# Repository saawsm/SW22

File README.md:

# SW22 - A modular E-Stim

---
**The SW22 is deprecated. See the [SW32 E-Stim](https://github.com/saawsm/SW32) for a better alternative.**

*This project is a work in-progress. Changes to the design might occur. Order PCBs at your own risk..*

---

## About
The SW22 is a modular E-Stim box based on the [ZC95](https://github.com/CrashOverride85/zc95) and the [WT-312](https://github.com/WendyTeslaburger/WT-312). 
It has a similar form factor and output design to the MK312-BT (which in turn is a clone of the ET-312B).

An <abbr title="ESP32-WROOM-32">ESP32</abbr> module is used for high level control (front panel controls, display, Bluetooth audio, etc) of the device, while an RP2040 microcontroller (RPi Pico) is used as a co-processor for pulse/routine generation (taking advantage of [PIO](https://raspberrypi.github.io/pico-sdk-doxygen/group__hardware__pio.html#details)). The firmware is open source and written in C.

Compared to the MK312-BT, it has two extra output channels, four auxiliary inputs, and four triggers. 

## Features
* Bluetooth A2DP*
* RS232 front panel serial
* 2x TRS 3.5mm Aux channels with expansion board support (e.g. Stereo Audio + Mono Microphone, RS232 Remote)
* 2x TRS 3.5mm Trigger channels
* Tri polar (+, GND, -) output channel support
* Modular output drivers per channel (Think: Sparkfun, Adafruit, etc.) incl. modular driver board.
* Individual channel sensing via quad 12-bit ADC
* 1.8" Color TFT display
* Support for an internal 0.96" I2C OLED display (e.g. debugging/testing)
* 256kb EEPROM for configuration
* Battery voltage monitoring
* Charge sense (Barrel jack voltage monitoring)

## Overview
The SW22 consists of following PCBs:
* Front Panel Cover - No traces, just the cosmetic front panel with text. Could be 3D printed or laser cut.
* Front Panel - I2C based expansion board with 4x POTs with associated ADC, 1x rotary encoder, 4x tactile buttons, 1x buzzer, and 8x addressable RGB LEDs.
* Base Board - Provides system power, battery charging, expansion, Bluetooth, front panel interface, and general control.
* Driver Board - Provides low-level control over channel output modules.
* Output Modules - Generates the E-Stim for each channel. A module per channel, controlled by the driver board. 
* Expansion Module (Optional) - Allows advanced configuration of Aux channels (e.g. Audio+Microphone)

The main reason for having modular PCBs is for flexibility and long term cost saving. Most of the cost and time that is involved in the project is the firmware, case, display, controls, etc. So being able to reuse parts when changing the design (e.g. new output modules, driver board, etc) should help keep time and cost down.

Additionally, the SW22 was designed with the front panel and display being optional accessories. Anything that can be achieved on the front panel, can be done via Bluetooth/WiFi. The driver board can be used as a standalone module (Think: Sparkfun, Adafruit, etc.).

## Build Notes
The majority of this build is SMT. I have tried to keep parts large enough (0603 and above) for manual pick and place. However, for a few components, no alternative was available (e.g. Driver board uses MSOP/VSSOP packages).

Most SMD components used are available from Mouser and LCSC. Front panel components being mostly available at places that aren't LCSC (pots, encoders, audio jacks, etc).

Some components have a thermal pad that will require a reflow oven or using hot air reflow soldering.

## [Schematics](schematics/)

## [Gerbers](gerbers/)
Gerbers are created for use with JLCPCB. P&P POS files untested/missing (since I assemble the PCBs myself).

## Firmware
The firmware is open source and written in C. You can find the source code in the [swef](https://github.com/saawsm/swef) and [swx](https://github.com/saawsm/swx) repositories.

`swef` and `swx` don't support SPI used by the SW22 for connection between the base and driver boards. Basic functionality requires adding additional bodge wires (SDA and SCL) between the base and driver boards.

This change was done to simplify communications and to prepare for the successor [SW32](https://github.com/saawsm/SW32) box.

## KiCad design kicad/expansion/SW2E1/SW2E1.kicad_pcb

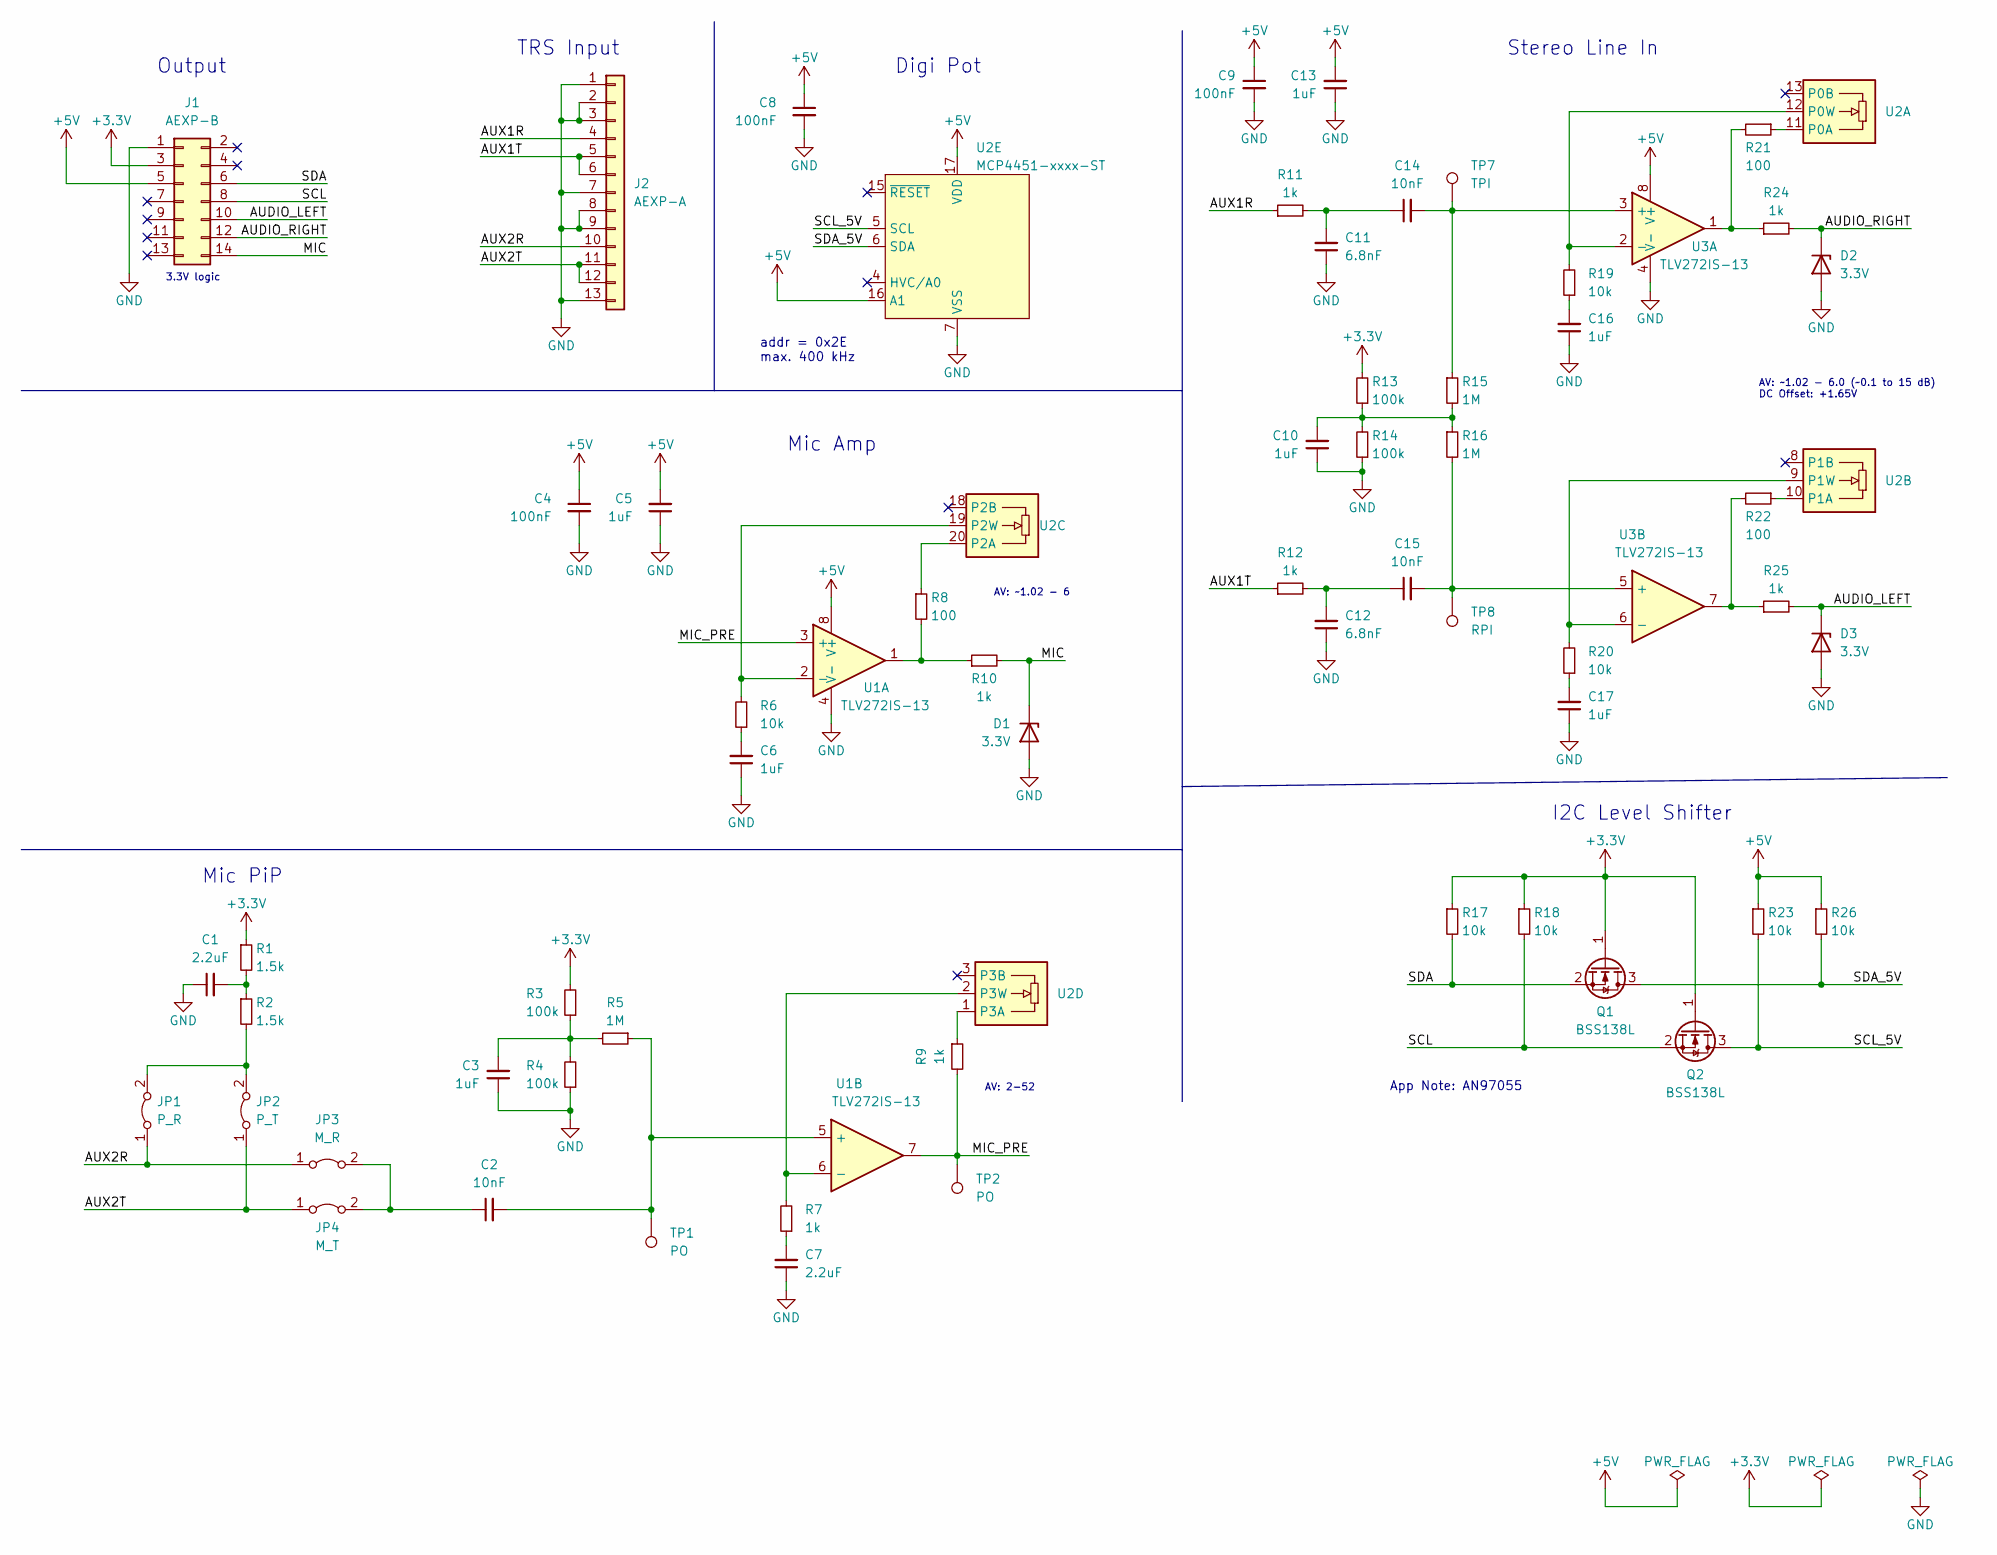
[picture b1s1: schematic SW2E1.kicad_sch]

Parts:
C1, C7: 2.2uF; C_0603_1608Metric
C2, C14, C15: 10nF; C_0603_1608Metric
C3, C5, C6, C10, C13, C16, C17: 1uF; C_0603_1608Metric
C4, C8, C9: 100nF; C_0603_1608Metric
C11, C12: 6.8nF; C_0603_1608Metric
D1, D2, D3: 3.3V; D_SOD-123F
J1: AEXP-B; PinHeader_2x07_P2.54mm_Vertical
J2: AEXP-A; PinHeader_1x13_P2.54mm_Vertical
JP1: P_R; PinHeader_1x02_P2.54mm_Vertical
JP2: P_T; PinHeader_1x02_P2.54mm_Vertical
JP3: M_R; PinHeader_1x02_P2.54mm_Vertical
JP4: M_T; PinHeader_1x02_P2.54mm_Vertical
Q1, Q2: BSS138L; SOT-23
R1, R2: 1.5k; R_0603_1608Metric
R3, R4, R13, R14: 100k; R_0603_1608Metric
R5, R15, R16: 1M; R_0603_1608Metric
R6, R17, R18, R19, R20, R23, R26: 10k; R_0603_1608Metric
R7, R9, R10, R11, R12, R24, R25: 1k; R_0603_1608Metric
R8, R21, R22: 100; R_0603_1608Metric
TP1, TP2: PO; TestPoint_Pad_D1.5mm
TP7: TPI; TestPoint_Pad_D1.5mm
TP8: RPI; TestPoint_Pad_D1.5mm
U1, U3: TLV272IS-13; SOIC-8_3.9x4.9mm_P1.27mm
U2: MCP4451-xxxx-ST; TSSOP-20_4.4x6.5mm_P0.65mm

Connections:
+3.3V: J1.3, Q1.1 (G), Q2.1 (G), R1.1, R3.2, R13.2, R17.1, R18.1
+5V: C4.1, C5.2, C8.1, C9.1, C13.2, J1.5, R23.1, R26.1, U1.8 (V+), U2.16 (A1), U2.17 (VDD), U3.8 (V+)
/AUDIO_LEFT: D3.1 (K), J1.10, R25.2
/AUDIO_RIGHT: D2.1 (K), J1.12, R24.2
/AUX1R: J2.4, R11.1
/AUX1T: J2.5, J2.6, R12.1
/AUX2R: J2.10, JP1.1 (A), JP3.1 (A)
/AUX2T: J2.11, J2.12, JP2.1 (A), JP4.1 (A)
/MIC: D1.1 (K), J1.14, R10.2
/MIC_PRE: R9.2, TP2.1, U1.3 (+), U1.7
/SCL: J1.8, Q2.2 (S), R18.2
/SCL_5V: Q2.3 (D), R23.2, U2.5 (SCL)
/SDA: J1.6, Q1.2 (S), R17.2
/SDA_5V: Q1.3 (D), R26.2, U2.6 (SDA)
GND: C1.1, C3.1, C4.2, C5.1, C6.1, C7.1, C8.2, C9.2, C10.1, C11.1, C12.1, C13.1, C16.1, C17.1, D1.2 (A), D2.2 (A), D3.2 (A), J1.1, J2.1, J2.2, J2.3, J2.7, J2.8, J2.9, J2.13, R4.1, R14.1, U1.4 (V-), U2.7 (VSS), U3.4 (V-)
unnamed: C1.2, R1.2, R2.1
unnamed: C2.1, JP3.2 (B), JP4.2 (B)
unnamed: C2.2, R5.1, TP1.1, U1.5 (+)
unnamed: C3.2, R3.1, R4.2, R5.2
unnamed: C6.2, R6.1
unnamed: C7.2, R7.1
unnamed: C10.2, R13.1, R14.2, R15.2, R16.1
unnamed: C11.2, C14.1, R11.2
unnamed: C12.2, C15.1, R12.2
unnamed: C14.2, R15.1, TP7.1, U3.3 (+)
unnamed: C15.2, R16.2, TP8.1, U3.5 (+)
unnamed: C16.2, R19.1
unnamed: C17.2, R20.1
unnamed: JP1.2 (B), JP2.2 (B), R2.2
unnamed: R6.2, U1.2 (-), U2.19 (P2W)
unnamed: R7.2, U1.6 (-), U2.2 (P3W)
unnamed: R8.1, U2.20 (P2A)
unnamed: R9.1, U2.1 (P3A)
unnamed: R8.2, R10.1, U1.1
unnamed: R19.2, U2.12 (P0W), U3.2 (-)
unnamed: R20.2, U2.9 (P1W), U3.6 (-)
unnamed: R21.1, U2.11 (P0A)
unnamed: R21.2, R24.1, U3.1
unnamed: R22.1, U2.10 (P1A)
unnamed: R22.2, R25.1, U3.7

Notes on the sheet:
I2C Level Shifter
App Note: AN97055
addr = 0x2E max. 400 kHz
TRS Input
Digi Pot
Mic PiP
Stereo Line In
Mic Amp
AV: ~1.02 - 6.0 (~0.1 to 15 dB) DC Offset: +1.65V
Output
AV: ~1.02 - 6
3.3V logic
AV: 2-52

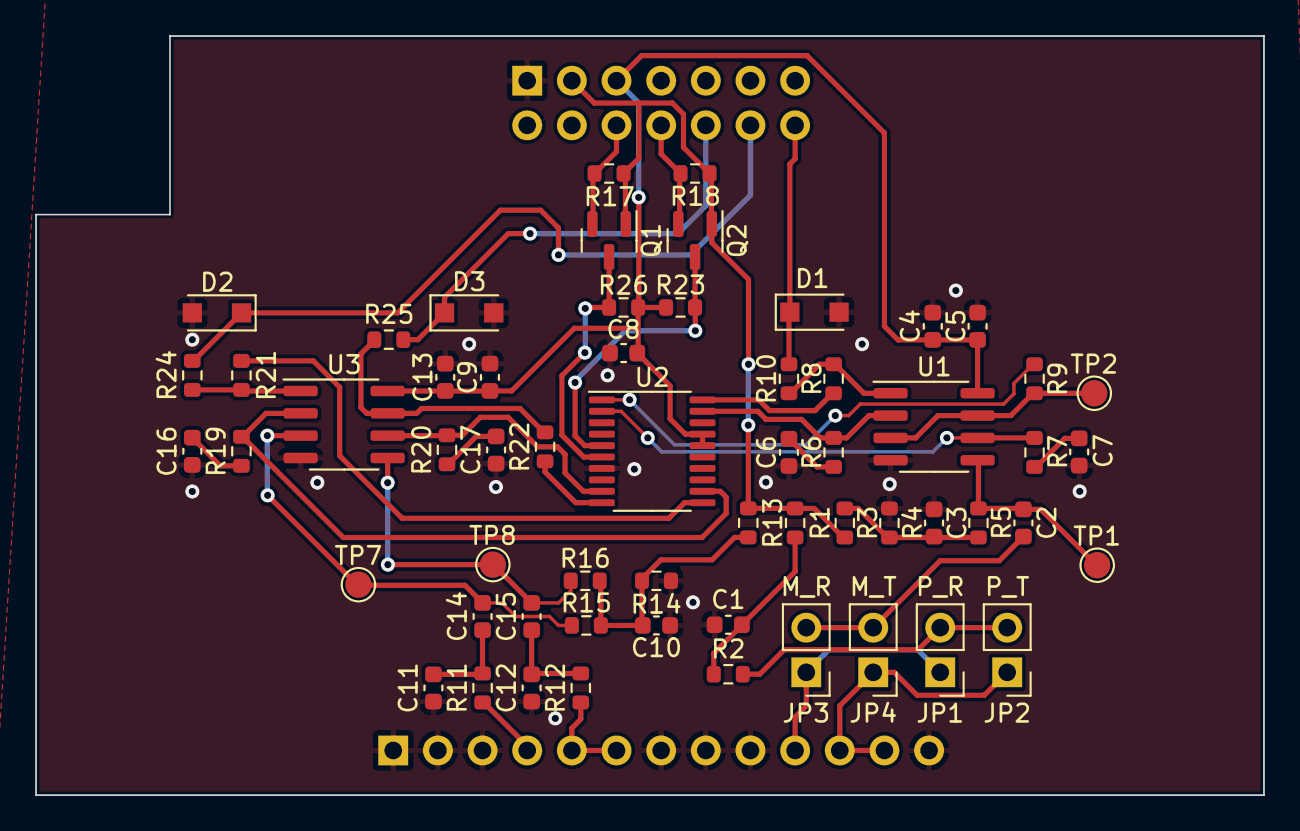
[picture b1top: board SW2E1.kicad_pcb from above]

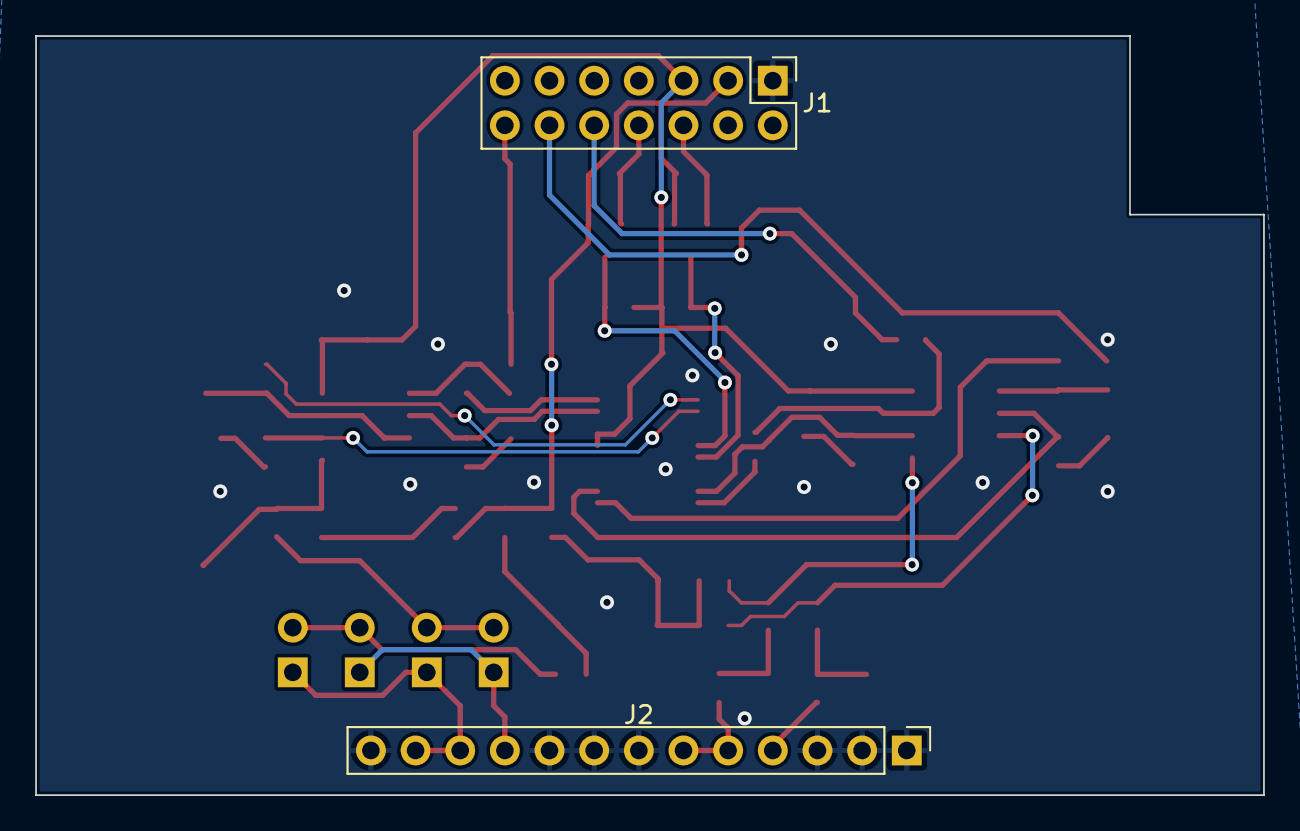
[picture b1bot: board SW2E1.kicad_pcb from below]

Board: 2 copper layers, 69.9 x 43.2 mm, 61 parts (2 on the bottom side), 40 nets.

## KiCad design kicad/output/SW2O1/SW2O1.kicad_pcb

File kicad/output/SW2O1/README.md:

## SW2O1 - Single Channel Output Module

This is a single channel E-Stim output module. It tries to mimic the output stage of the well-known Erostec ET312, or better, the MK-312.

The design of this module was based on the [WT-312](https://github.com/WendyTeslaburger/WT-312).

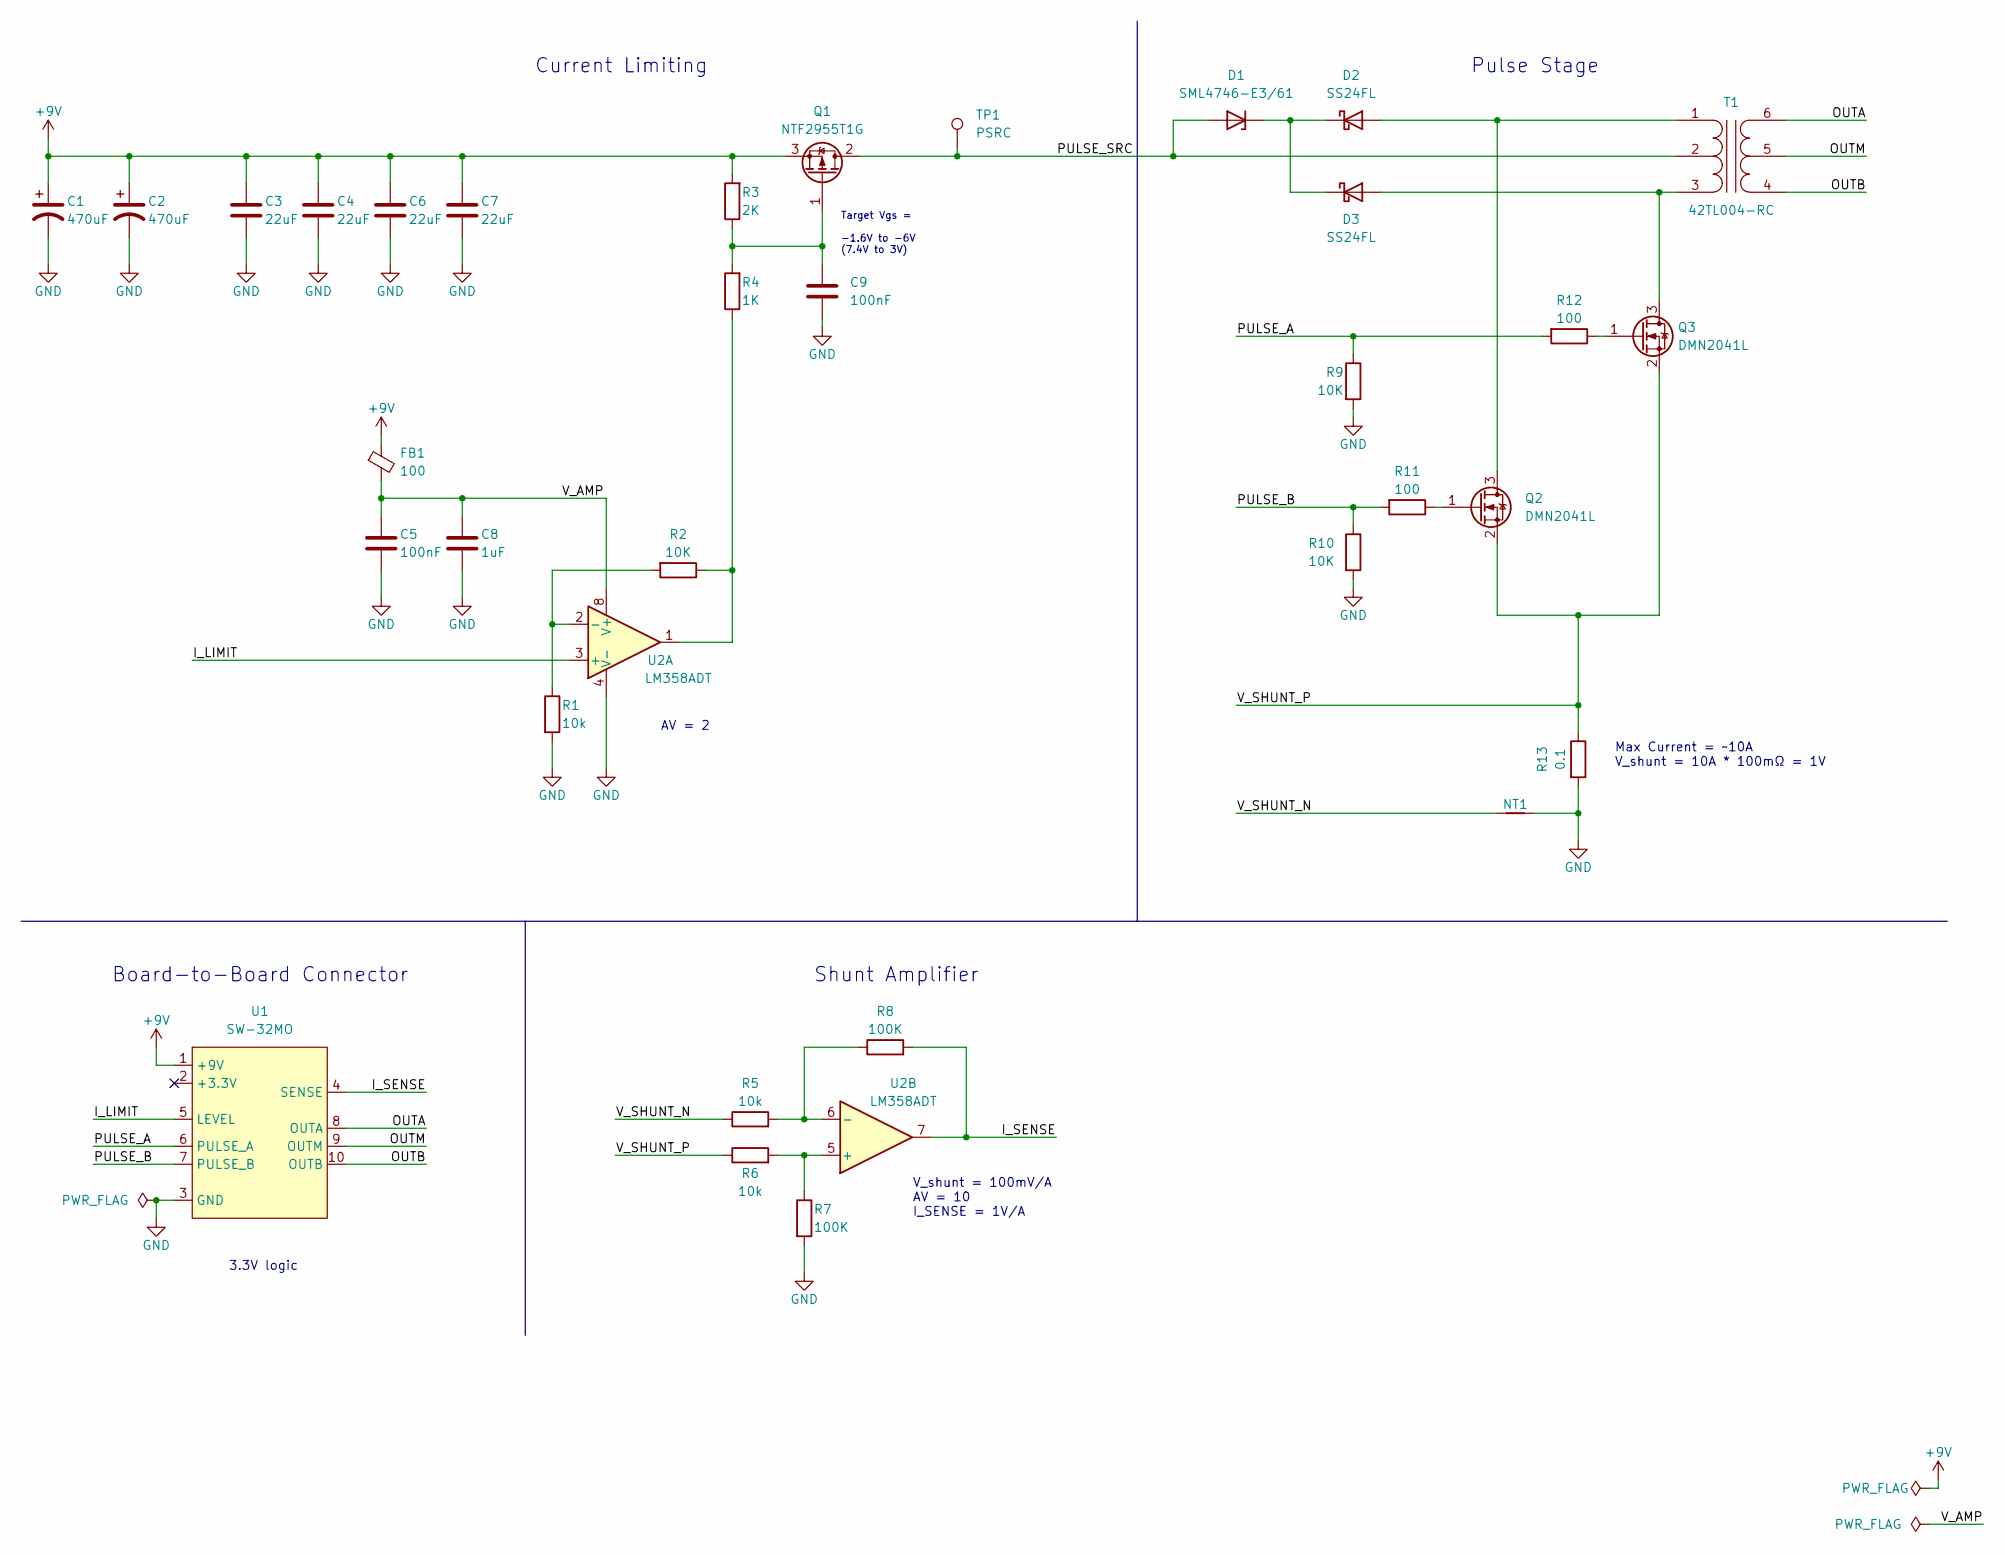
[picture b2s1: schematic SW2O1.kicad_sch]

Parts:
C1, C2: 470uF; CP_Radial_D8.0mm_P3.50mm; MPN 477CKE016M
C3, C4, C6, C7: 22uF; C_1210_3225Metric; MPN CL32A226KAJNNNE
C5, C9: 100nF; C_0603_1608Metric; MPN CL10B104KB8NNWC
C8: 1uF; C_0603_1608Metric; MPN CL10B105KA8NFNC
D1: SML4746-E3/61; D_SMA; MPN SML4746-E3/61
D2: SS24FL; D_SOD-123F; MPN SS24FL; LCSC C894433
D3: SS24FL; D_SOD-123F; MPN SS24FL; MOUSER 512-SS24FL
FB1: 100; R_0603_1608Metric; MPN BLM18KG101TN1D
NT1: 0.5 mm; NetTie-2_SMD_Pad0.5mm
Q1: NTF2955T1G; SOT-223-3_TabPin2; MPN NTF2955T1G
Q2, Q3: DMN2041L; SOT-23; MPN DMN2041L
R1, R5, R6: 10k; R_0603_1608Metric; MPN RC0603FR-0710KL
R2, R9, R10: 10K; R_0603_1608Metric; MPN RC0603FR-0710KL
R3: 2K; R_0603_1608Metric; MPN RC0603FR-072KL
R4: 1K; R_0603_1608Metric; MPN RC0603FR-071KL
R7, R8: 100K; R_0603_1608Metric; MPN RC0603FR-07100KL
R11, R12: 100; R_0603_1608Metric; MPN RC0603FR-07100RL
R13: 0.1; R_1206_3216Metric; MPN ERJ-8BWFR100V
T1: 42TL004-RC; 42TL; MPN 42TL004-RC
TP1: PSRC; TestPoint_Pad_D1.5mm
U1: SW-32MO; SW32-MO_Header
U2: LM358ADT; SOIC-8_3.9x4.9mm_P1.27mm; MPN LM358ADT

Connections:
+9V: C1.1, C2.1, C3.1, C4.1, C6.1, C7.1, FB1.1, Q1.3 (S), R3.2, U1.1 (+9V)
/I_LIMIT: U1.5 (LEVEL), U2.3 (+)
/I_SENSE: R8.2, U1.4 (SENSE), U2.7
/OUTA: T1.6 (S2), U1.8 (OUTA)
/OUTB: T1.4 (S1), U1.10 (OUTB)
/OUTM: T1.5 (SM), U1.9 (OUTM)
/PULSE_A: R9.1, R12.2, U1.6 (PULSE_A)
/PULSE_B: R10.1, R11.2, U1.7 (PULSE_B)
/PULSE_SRC: D1.2 (A), Q1.2 (D), T1.2 (PM), TP1.1
/V_AMP: C5.1, C8.1, FB1.2, U2.8 (V+)
/V_SHUNT_N: NT1.1, R5.1
/V_SHUNT_P: Q2.2 (S), Q3.2 (S), R6.1, R13.1
GND: C1.2, C2.2, C3.2, C4.2, C5.2, C6.2, C7.2, C8.2, C9.1, NT1.2, R1.2, R7.2, R9.2, R10.2, R13.2, U1.3 (GND), U2.4 (V-)
unnamed: C9.2, Q1.1 (G), R3.1, R4.2
unnamed: D1.1 (K), D2.1 (K), D3.1 (K)
unnamed: D2.2 (A), Q2.3 (D), T1.1 (PR1)
unnamed: D3.2 (A), Q3.3 (D), T1.3 (PR2)
unnamed: Q2.1 (G), R11.1
unnamed: Q3.1 (G), R12.1
unnamed: R1.1, R2.2, U2.2 (-)
unnamed: R2.1, R4.1, U2.1
unnamed: R5.2, R8.1, U2.6 (-)
unnamed: R6.2, R7.1, U2.5 (+)

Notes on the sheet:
Max Current = ~10A V_shunt = 10A * 100mΩ = 1V
Board-to-Board Connector
V_shunt = 100mV/A AV = 10 I_SENSE = 1V/A
AV = 2
Shunt Amplifier
Pulse Stage
Target Vgs = -1.6V to -6V (7.4V to 3V)
Current Limiting
3.3V logic

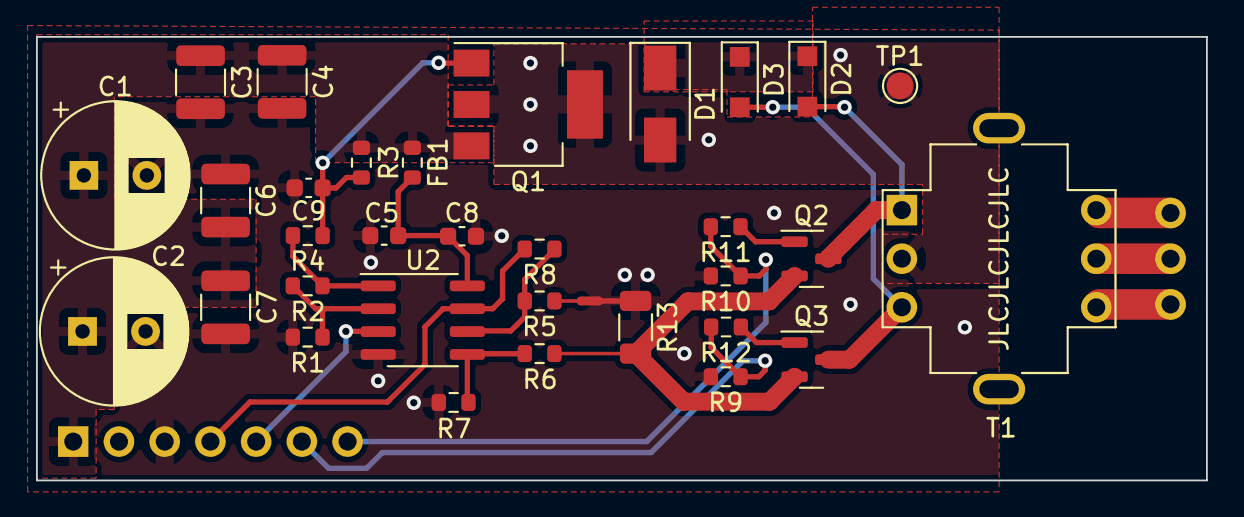
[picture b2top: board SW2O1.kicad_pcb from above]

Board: 2 copper layers, 65.0 x 24.6 mm, 34 parts (0 on the bottom side), 23 nets.

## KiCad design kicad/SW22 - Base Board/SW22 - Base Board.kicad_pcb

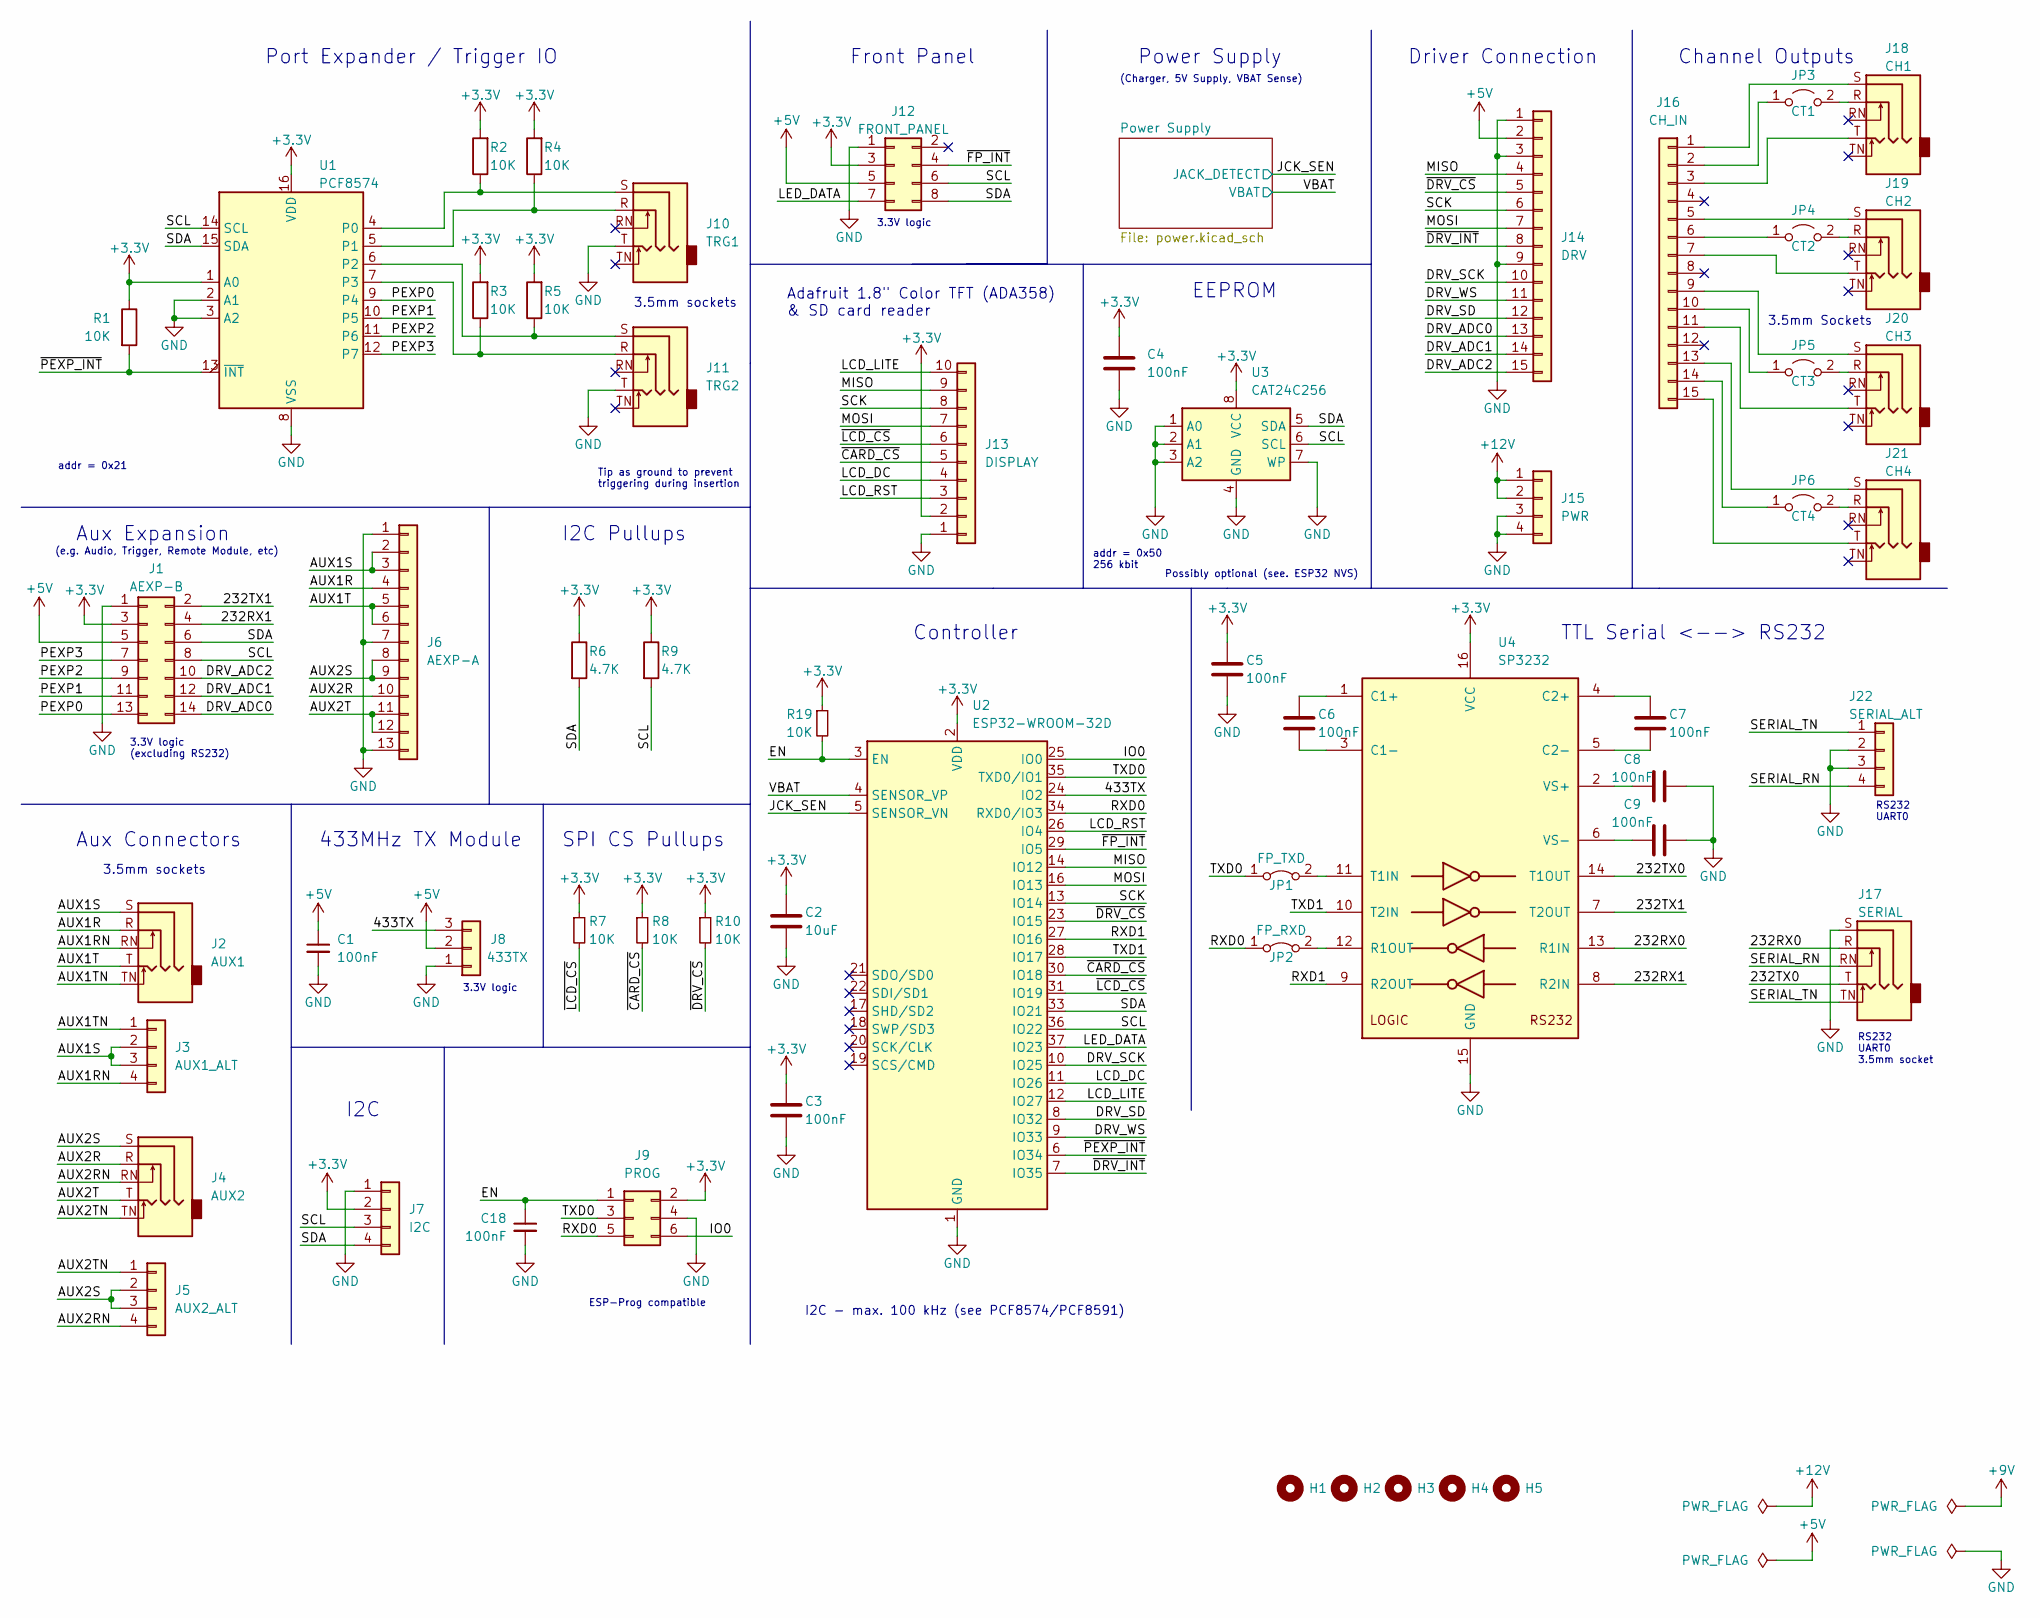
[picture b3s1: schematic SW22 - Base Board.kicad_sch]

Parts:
C1, C3, C4, C5, C6, C7, C8, C9, C18: 100nF; C_0603_1608Metric; MPN CL10B104KB8NNNC; LCSC C1591
C2: 10uF; C_0603_1608Metric; MPN CL10A106MA8NRNC; LCSC C96446
H1, H2, H3, H4, H5: MountingHole; MountingHole_2.2mm_M2
J1: AEXP-B; PinSocket_2x07_P2.54mm_Vertical
J2: AUX1; STX-3100-5N; MPN STX-3100-5N; MOUSER 806-STX-3100-5N
J3: AUX1_ALT; PinHeader_1x04_P2.54mm_Vertical
J4: AUX2; STX-3100-5N; MPN STX-3100-5N; MOUSER 806-STX-3100-5N
J5: AUX2_ALT; PinHeader_1x04_P2.54mm_Vertical
J6: AEXP-A; PinSocket_1x13_P2.54mm_Vertical
J7: I2C; PinHeader_1x04_P2.54mm_Vertical
J8: 433TX; PinSocket_1x03_P2.54mm_Vertical
J9: PROG; IDC-Header_2x03_P2.54mm_Vertical
J10: TRG1; STX-3100-5N; MPN STX-3100-5N; MOUSER 806-STX-3100-5N
J11: TRG2; STX-3100-5N; MPN STX-3100-5N; MOUSER 806-STX-3100-5N
J12: FRONT_PANEL; IDC-Header_2x04_P2.54mm_Vertical
J13: DISPLAY; PinHeader_1x10_P2.54mm_Vertical
J14: DRV; PinSocket_1x15_P2.54mm_Vertical
J15: PWR; PinSocket_1x04_P2.54mm_Vertical
J16: CH_IN; PinSocket_1x15_P2.54mm_Vertical
J17: SERIAL; STX-3100-5N; MPN STX-3100-5N; MOUSER 806-STX-3100-5N
J18: CH1; STX-3100-5N; MPN STX-3100-5N; MOUSER 806-STX-3100-5N
J19: CH2; STX-3100-5N; MPN STX-3100-5N; MOUSER 806-STX-3100-5N
J20: CH3; STX-3100-5N; MPN STX-3100-5N; MOUSER 806-STX-3100-5N
J21: CH4; STX-3100-5N; MPN STX-3100-5N; MOUSER 806-STX-3100-5N
J22: SERIAL_ALT; PinHeader_1x04_P2.54mm_Vertical
JP1: FP_TXD; PinHeader_1x02_P2.54mm_Vertical
JP2: FP_RXD; PinHeader_1x02_P2.54mm_Vertical
JP3: CT1; PinHeader_1x02_P2.54mm_Vertical
JP4: CT2; PinHeader_1x02_P2.54mm_Vertical
JP5: CT3; PinHeader_1x02_P2.54mm_Vertical
JP6: CT4; PinHeader_1x02_P2.54mm_Vertical
R1, R2, R3, R4, R5, R7, R8, R10, R19: 10K; R_0603_1608Metric; MPN RC0603FR-0710KL; MOUSER 603-RC0603FR-0710KL
R6, R9: 4.7K; R_0603_1608Metric; MPN RC0603FR-074K7L; MOUSER 603-RC0603FR-074K7L
U1: PCF8574; SOIC-16W_7.5x10.3mm_P1.27mm; MPN PCF8574T/3,512; LCSC C1522621
U2: ESP32-WROOM-32D; ESP32-WROOM-32; MPN ESP32-WROOM-32D-N16
U3: CAT24C256; SOIC-8_3.9x4.9mm_P1.27mm; MPN CAT24C256WI-GT3; LCSC C79987
U4: SP3232; SOIC-16_3.9x9.9mm_P1.27mm; MPN SP3232EEN-L/TR; LCSC C9378

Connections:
+3.3V: C2.1, C3.2, C4.2, C5.2, J1.3, J7.2, J9.2, J12.3, J13.2, R1.1, R2.2, R3.2, R4.2, R5.2, R6.1, R7.1, R8.1, R9.1, R10.1, R19.1, U1.1 (A0), U1.16 (VDD), U2.2 (VDD), U3.8 (VCC), U4.16 (VCC); also elsewhere on the board
+5V: C1.1, J1.5, J8.2, J12.5, J14.2; also elsewhere on the board
+12V: J15.1, J15.2; also elsewhere on the board
/232RX0: J17.R, U4.13 (R1IN)
/232RX1: J1.4, U4.8 (R2IN)
/232TX0: J17.T, U4.14 (T1OUT)
/232TX1: J1.2, U4.7 (T2OUT)
/433TX: J8.3, U2.24 (IO2)
/AUX1R: J2.R, J6.4
/AUX1RN: J2.RN, J3.4
/AUX1S: J2.S, J3.2, J3.3, J6.2, J6.3
/AUX1T: J2.T, J6.5, J6.6
/AUX1TN: J2.TN, J3.1
/AUX2R: J4.R, J6.10
/AUX2RN: J4.RN, J5.4
/AUX2S: J4.S, J5.2, J5.3, J6.8, J6.9
/AUX2T: J4.T, J6.11, J6.12
/AUX2TN: J4.TN, J5.1
/DRV_ADC0: J1.14, J14.13
/DRV_ADC1: J1.12, J14.14
/DRV_ADC2: J1.10, J14.15
/DRV_SCK: J14.10, U2.10 (IO25)
/DRV_SD: J14.12, U2.8 (IO32)
/DRV_WS: J14.11, U2.9 (IO33)
/EN: C18.1, J9.1, R19.2, U2.3 (EN)
/IO0: J9.6, U2.25 (IO0)
/JCK_SEN: U2.5 (SENSOR_VN); also elsewhere on the board
/LCD_DC: J13.4, U2.11 (IO26)
/LCD_LITE: J13.10, U2.12 (IO27)
/LCD_RST: J13.3, U2.26 (IO4)
/LED_DATA: J12.7, U2.37 (IO23)
/MISO: J13.9, J14.4, U2.14 (IO12)
/MOSI: J13.7, J14.7, U2.16 (IO13)
/PEXP0: J1.13, U1.9 (P4)
/PEXP1: J1.11, U1.10 (P5)
/PEXP2: J1.9, U1.11 (P6)
/PEXP3: J1.7, U1.12 (P7)
/RXD0: J9.5, JP2.1 (A), U2.34 (RXD0/IO3); also elsewhere on the board
/RXD1: U2.27 (IO16), U4.9 (R2OUT)
/SCK: J13.8, J14.6, U2.13 (IO14)
/SCL: J1.8, J7.3, J12.6, R9.2, U1.14 (SCL), U2.36 (IO22), U3.6 (SCL)
/SDA: J1.6, J7.4, J12.8, R6.2, U1.15 (SDA), U2.33 (IO21), U3.5 (SDA)
/SERIAL_RN: J17.RN, J22.4
/SERIAL_TN: J17.TN, J22.1
/TXD0: J9.3, JP1.1 (A), U2.35 (TXD0/IO1)
/TXD1: U2.28 (IO17), U4.10 (T2IN)
/VBAT: U2.4 (SENSOR_VP); also elsewhere on the board
/~CARD_CS: J13.5, R8.2, U2.30 (IO18)
/~DRV_CS: J14.5, R10.2, U2.23 (IO15)
/~DRV_INT: J14.8, U2.7 (IO35)
/~FP_INT: J12.4, U2.29 (IO5)
/~LCD_CS: J13.6, R7.2, U2.31 (IO19)
/~PEXP_INT: R1.2, U1.13 (~INT), U2.6 (IO34)
GND: C1.2, C2.2, C3.1, C4.1, C5.1, C8.1, C9.1, C18.2, J1.1, J6.1, J6.7, J6.13, J7.1, J8.1, J9.4, J10.T, J11.T, J12.1, J13.1, J14.1, J14.3, J14.9, J15.3, J15.4, J17.S, J22.2, J22.3, U1.2 (A1), U1.3 (A2), U1.8 (VSS), U2.1 (GND), U2.15 (GND), U2.38 (GND), U2.39 (GND), U3.1 (A0), U3.2 (A1), U3.3 (A2), U3.4 (GND), U3.7 (WP), U4.15 (GND); also elsewhere on the board
unnamed: C6.1, U4.3 (C1-)
unnamed: C6.2, U4.1 (C1+)
unnamed: C7.1, U4.5 (C2-)
unnamed: C7.2, U4.4 (C2+)
unnamed: C8.2, U4.2 (VS+)
unnamed: C9.2, U4.6 (VS-)
unnamed: J10.R, R4.1, U1.5 (P1)
unnamed: J10.S, R2.1, U1.4 (P0)
unnamed: J11.R, R3.1, U1.7 (P3)
unnamed: J11.S, R5.1, U1.6 (P2)
unnamed: J16.1, J18.S
unnamed: J16.2, JP3.1 (A)
unnamed: J16.3, J18.T
unnamed: J16.5, J19.S
unnamed: J16.6, JP4.1 (A)
unnamed: J16.7, J19.T
unnamed: J16.9, J20.S
unnamed: J16.10, JP5.1 (A)
unnamed: J16.11, J20.T
unnamed: J16.13, J21.S
unnamed: J16.14, JP6.1 (A)
unnamed: J16.15, J21.T
unnamed: J18.R, JP3.2 (B)
unnamed: J19.R, JP4.2 (B)
unnamed: J20.R, JP5.2 (B)
unnamed: J21.R, JP6.2 (B)
unnamed: JP1.2 (B), U4.11 (T1IN)
unnamed 89: JP2.2 (B), U4.12 (R1OUT); also elsewhere on the board

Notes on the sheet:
EEPROM
addr = 0x21
Adafruit 1.8" Color TFT (ADA358) & SD card reader
433MHz TX Module
I2C
(e.g. Audio, Trigger, Remote Module, etc)
Aux Connectors
3.3V logic (excluding RS232)
Tip as ground to prevent triggering during insertion
3.5mm sockets
3.3V logic
Possibly optional (see. ESP32 NVS)
Port Expander / Trigger IO
addr = 0x50 256 kbit
I2C Pullups
(Charger, 5V Supply, VBAT Sense)
ESP-Prog compatible
RS232 UART0 3.5mm socket
3.5mm Sockets
Power Supply
Driver Connection
SPI CS Pullups
I2C - max. 100 kHz (see PCF8574/PCF8591)
TTL Serial <--> RS232
Channel Outputs
Aux Expansion
Controller
Front Panel
RS232 UART0
